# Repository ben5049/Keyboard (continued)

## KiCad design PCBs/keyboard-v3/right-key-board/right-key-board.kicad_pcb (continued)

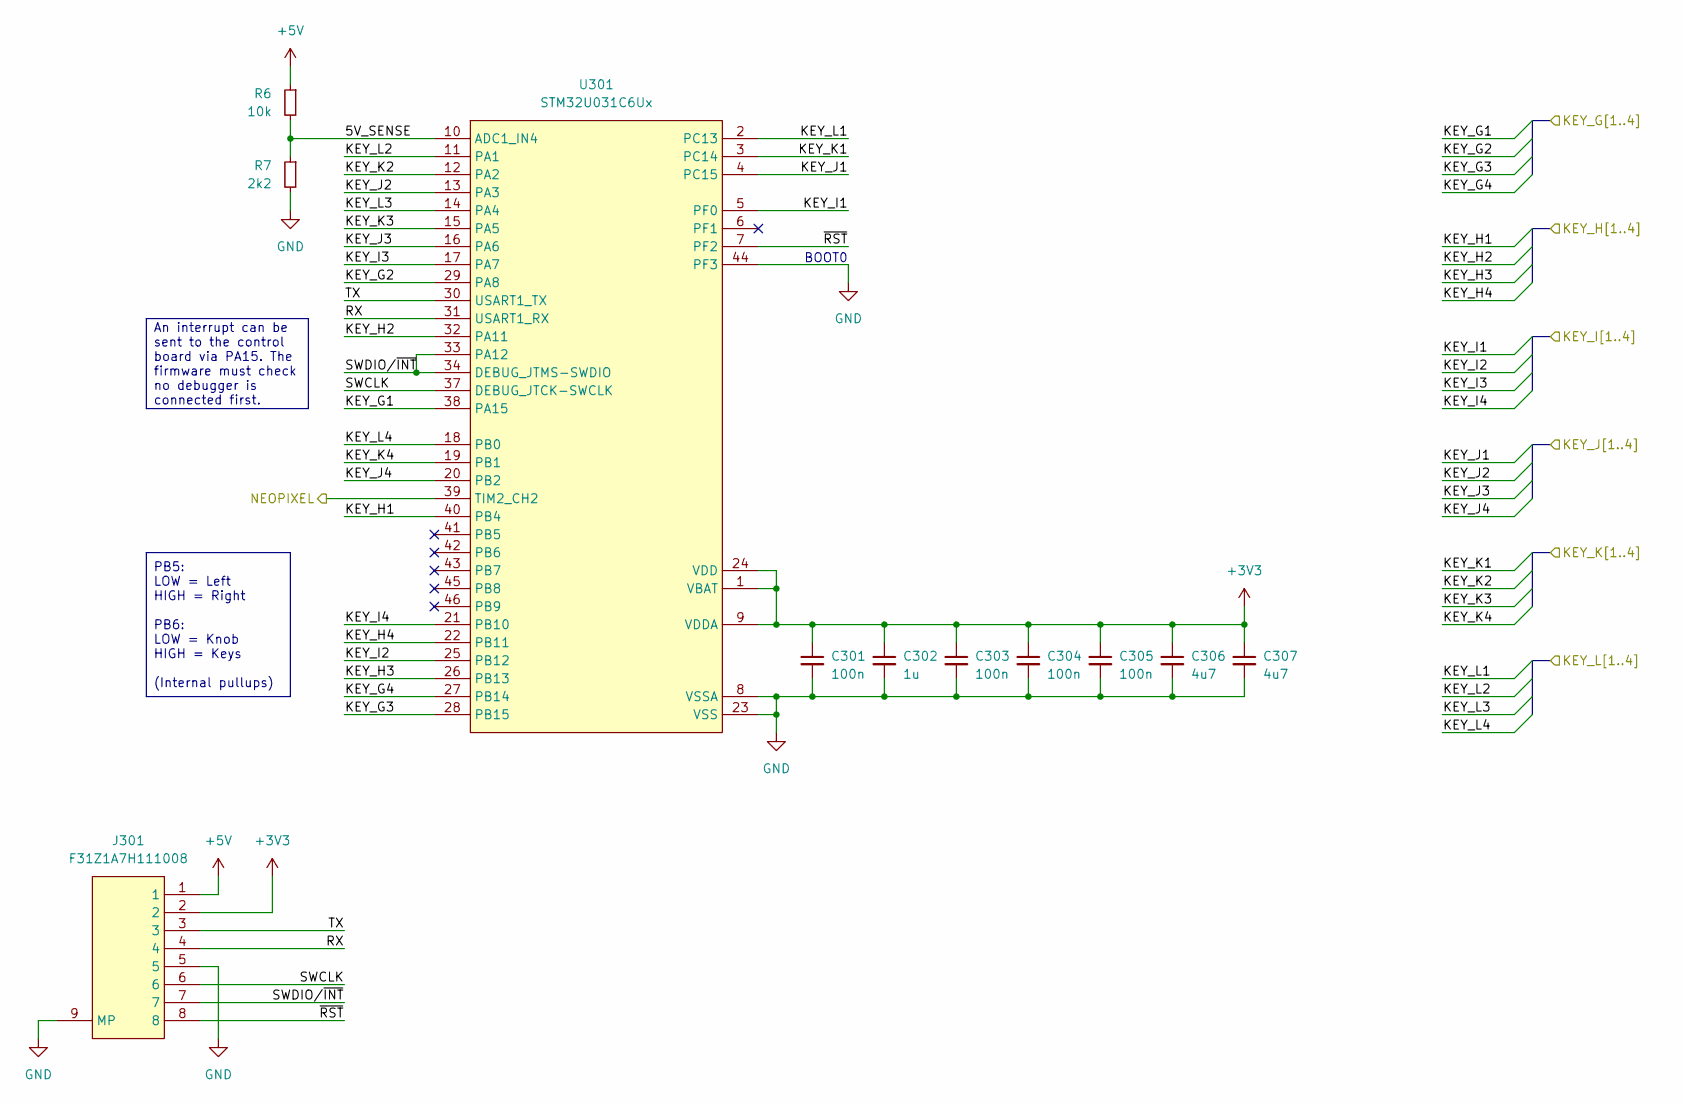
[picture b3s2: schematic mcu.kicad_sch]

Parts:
C301, C303, C304, C305: 100n; C_0402
C302: 1u; C_0402
C306, C307: 4u7; C_0402
J301: F31Z1A7H111008
R6: 10k; R_0402
R7: 2k2; R_0402
U301: STM32U031C6Ux; QFN50P700X700X60-49N-D

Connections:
+3V3: C301.1, C302.1, C303.1, C304.1, C305.1, C306.1, C307.1, J301.2, U301.1 (VBAT), U301.9 (VDDA), U301.24 (VDD), U301.36 (VDD), U301.48 (VDD)
+5V: J301.1, R6.1; also elsewhere on the board
/Keys/KEY_G1: U301.38 (PA15); also elsewhere on the board
/Keys/KEY_G2: U301.29 (PA8); also elsewhere on the board
/Keys/KEY_G3: U301.28 (PB15); also elsewhere on the board
/Keys/KEY_G4: U301.27 (PB14); also elsewhere on the board
/Keys/KEY_H1: U301.40 (PB4); also elsewhere on the board
/Keys/KEY_H2: U301.32 (PA11); also elsewhere on the board
/Keys/KEY_H3: U301.26 (PB13); also elsewhere on the board
/Keys/KEY_H4: U301.22 (PB11); also elsewhere on the board
/Keys/KEY_I1: U301.5 (PF0); also elsewhere on the board
/Keys/KEY_I2: U301.25 (PB12); also elsewhere on the board
/Keys/KEY_I3: U301.17 (PA7); also elsewhere on the board
/Keys/KEY_I4: U301.21 (PB10); also elsewhere on the board
/Keys/KEY_J1: U301.4 (PC15); also elsewhere on the board
/Keys/KEY_J2: U301.13 (PA3); also elsewhere on the board
/Keys/KEY_J3: U301.16 (PA6); also elsewhere on the board
/Keys/KEY_J4: U301.20 (PB2); also elsewhere on the board
/Keys/KEY_K1: U301.3 (PC14); also elsewhere on the board
/Keys/KEY_K2: U301.12 (PA2); also elsewhere on the board
/Keys/KEY_K3: U301.15 (PA5); also elsewhere on the board
/Keys/KEY_K4: U301.19 (PB1); also elsewhere on the board
/Keys/KEY_L1: U301.2 (PC13); also elsewhere on the board
/Keys/KEY_L2: U301.11 (PA1); also elsewhere on the board
/Keys/KEY_L3: U301.14 (PA4); also elsewhere on the board
/Keys/KEY_L4: U301.18 (PB0); also elsewhere on the board
/Keys/NEOPIXEL: U301.39 (TIM2_CH2); also elsewhere on the board
/MCU/5V_SENSE: R6.2, R7.1, U301.10 (ADC1_IN4)
/MCU/RX: J301.4, U301.31 (USART1_RX)
/MCU/SWCLK: J301.6, U301.37 (DEBUG_JTCK-SWCLK)
/MCU/SWDIO/~INT: J301.7, U301.33 (PA12), U301.34 (DEBUG_JTMS-SWDIO)
/MCU/TX: J301.3, U301.30 (USART1_TX)
/MCU/~RST: J301.8, U301.7 (PF2)
GND: C301.2, C302.2, C303.2, C304.2, C305.2, C306.2, C307.2, J301.5, J301.9 (MP), J301.10 (MP), J301.11 (MP), J301.12 (MP), R7.2, U301.8 (VSSA), U301.23 (VSS), U301.35 (VSS), U301.44 (PF3), U301.47 (VSS), U301.49 (VSS); also elsewhere on the board

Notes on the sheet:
BOOT0
An interrupt can be sent to the control board via PA15. The firmware must check no debugger is connected first.
PB5: LOW = Left HIGH = Right PB6: LOW = Knob HIGH = Keys (Internal pullups)

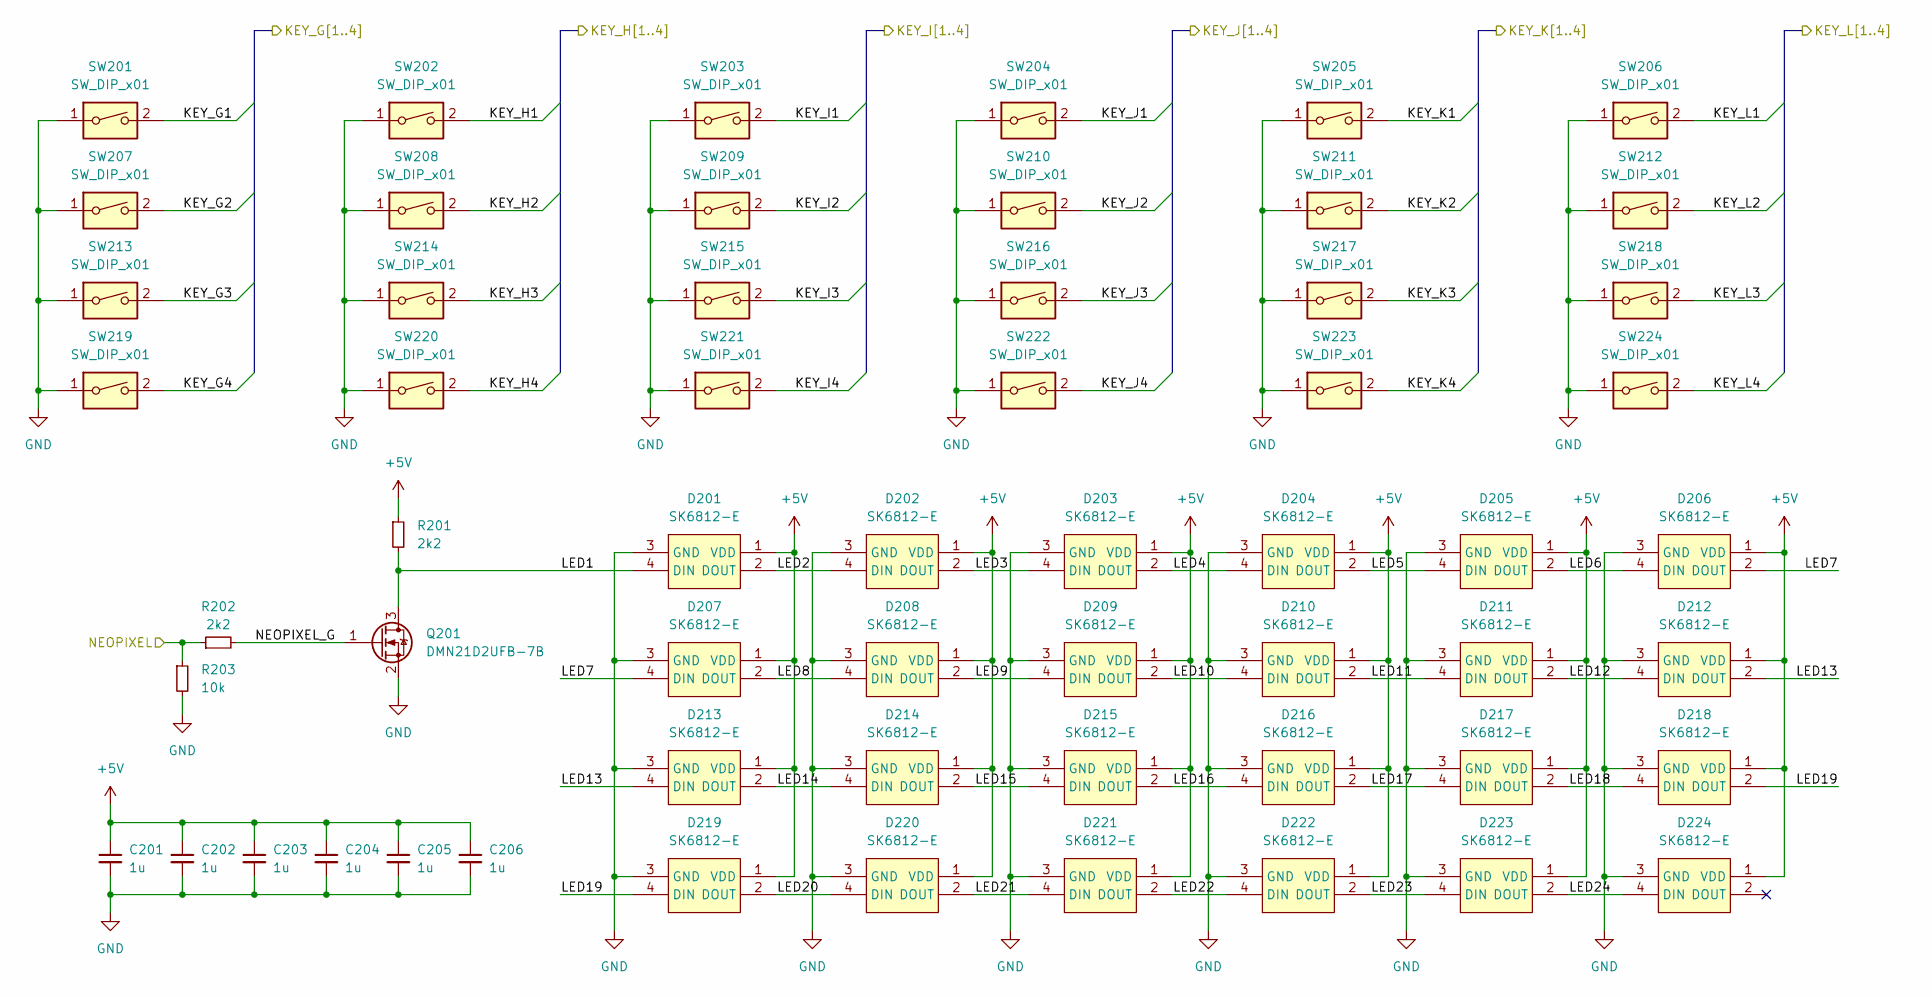
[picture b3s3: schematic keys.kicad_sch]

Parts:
C201, C202, C203, C204, C205, C206: 1u; C_0402
D201, D202, D203, D204, D205, D206, D207, D208, D209, D210, D211, D212, D213, D214, D215, D216, D217, D218, D219, D220, D221, D222, D223, D224: SK6812-E; sk6812-e; PARTREV 2
Q201: DMN21D2UFB-7B; DMN21D2UFB7B; Mouser Part Number 621-DMN21D2UFB-7B
R201, R202: 2k2; R_0402
R203: 10k; R_0402
SW201, SW202, SW203, SW204, SW205, SW206, SW207, SW208, SW209, SW210, SW211, SW212, SW213, SW214, SW215, SW216, SW217, SW218, SW219, SW220, SW221, SW222, SW223, SW224: SW_DIP_x01; SW_Kailh_Choc_V1_HotSwap

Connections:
+5V: C201.1, C202.1, C203.1, C204.1, C205.1, C206.1, D201.1 (VDD), D202.1 (VDD), D203.1 (VDD), D204.1 (VDD), D205.1 (VDD), D206.1 (VDD), D207.1 (VDD), D208.1 (VDD), D209.1 (VDD), D210.1 (VDD), D211.1 (VDD), D212.1 (VDD), D213.1 (VDD), D214.1 (VDD), D215.1 (VDD), D216.1 (VDD), D217.1 (VDD), D218.1 (VDD), D219.1 (VDD), D220.1 (VDD), D221.1 (VDD), D222.1 (VDD), D223.1 (VDD), D224.1 (VDD), R201.1; also elsewhere on the board
/Keys/KEY_G1: SW201.2; also elsewhere on the board
/Keys/KEY_G2: SW207.2; also elsewhere on the board
/Keys/KEY_G3: SW213.2; also elsewhere on the board
/Keys/KEY_G4: SW219.2; also elsewhere on the board
/Keys/KEY_H1: SW202.2; also elsewhere on the board
/Keys/KEY_H2: SW208.2; also elsewhere on the board
/Keys/KEY_H3: SW214.2; also elsewhere on the board
/Keys/KEY_H4: SW220.2; also elsewhere on the board
/Keys/KEY_I1: SW203.2; also elsewhere on the board
/Keys/KEY_I2: SW209.2; also elsewhere on the board
/Keys/KEY_I3: SW215.2; also elsewhere on the board
/Keys/KEY_I4: SW221.2; also elsewhere on the board
/Keys/KEY_J1: SW204.2; also elsewhere on the board
/Keys/KEY_J2: SW210.2; also elsewhere on the board
/Keys/KEY_J3: SW216.2; also elsewhere on the board
/Keys/KEY_J4: SW222.2; also elsewhere on the board
/Keys/KEY_K1: SW205.2; also elsewhere on the board
/Keys/KEY_K2: SW211.2; also elsewhere on the board
/Keys/KEY_K3: SW217.2; also elsewhere on the board
/Keys/KEY_K4: SW223.2; also elsewhere on the board
/Keys/KEY_L1: SW206.2; also elsewhere on the board
/Keys/KEY_L2: SW212.2; also elsewhere on the board
/Keys/KEY_L3: SW218.2; also elsewhere on the board
/Keys/KEY_L4: SW224.2; also elsewhere on the board
/Keys/LED1: D201.4 (DIN), Q201.3 (D), R201.2
/Keys/LED2: D201.2 (DOUT), D202.4 (DIN)
/Keys/LED3: D202.2 (DOUT), D203.4 (DIN)
/Keys/LED4: D203.2 (DOUT), D204.4 (DIN)
/Keys/LED5: D204.2 (DOUT), D205.4 (DIN)
/Keys/LED6: D205.2 (DOUT), D206.4 (DIN)
/Keys/LED7: D206.2 (DOUT), D207.4 (DIN)
/Keys/LED8: D207.2 (DOUT), D208.4 (DIN)
/Keys/LED9: D208.2 (DOUT), D209.4 (DIN)
/Keys/LED10: D209.2 (DOUT), D210.4 (DIN)
/Keys/LED11: D210.2 (DOUT), D211.4 (DIN)
/Keys/LED12: D211.2 (DOUT), D212.4 (DIN)
/Keys/LED13: D212.2 (DOUT), D213.4 (DIN)
/Keys/LED14: D213.2 (DOUT), D214.4 (DIN)
/Keys/LED15: D214.2 (DOUT), D215.4 (DIN)
/Keys/LED16: D215.2 (DOUT), D216.4 (DIN)
/Keys/LED17: D216.2 (DOUT), D217.4 (DIN)
/Keys/LED18: D217.2 (DOUT), D218.4 (DIN)
/Keys/LED19: D218.2 (DOUT), D219.4 (DIN)
/Keys/LED20: D219.2 (DOUT), D220.4 (DIN)
/Keys/LED21: D220.2 (DOUT), D221.4 (DIN)
/Keys/LED22: D221.2 (DOUT), D222.4 (DIN)
/Keys/LED23: D222.2 (DOUT), D223.4 (DIN)
/Keys/LED24: D223.2 (DOUT), D224.4 (DIN)
/Keys/NEOPIXEL: R202.1, R203.1; also elsewhere on the board
/Keys/NEOPIXEL_G: Q201.1 (G), R202.2
GND: C201.2, C202.2, C203.2, C204.2, C205.2, C206.2, D201.3 (GND), D202.3 (GND), D203.3 (GND), D204.3 (GND), D205.3 (GND), D206.3 (GND), D207.3 (GND), D208.3 (GND), D209.3 (GND), D210.3 (GND), D211.3 (GND), D212.3 (GND), D213.3 (GND), D214.3 (GND), D215.3 (GND), D216.3 (GND), D217.3 (GND), D218.3 (GND), D219.3 (GND), D220.3 (GND), D221.3 (GND), D222.3 (GND), D223.3 (GND), D224.3 (GND), Q201.2 (S), R203.2, SW201.1, SW202.1, SW203.1, SW204.1, SW205.1, SW206.1, SW207.1, SW208.1, SW209.1, SW210.1, SW211.1, SW212.1, SW213.1, SW214.1, SW215.1, SW216.1, SW217.1, SW218.1, SW219.1, SW220.1, SW221.1, SW222.1, SW223.1, SW224.1; also elsewhere on the board

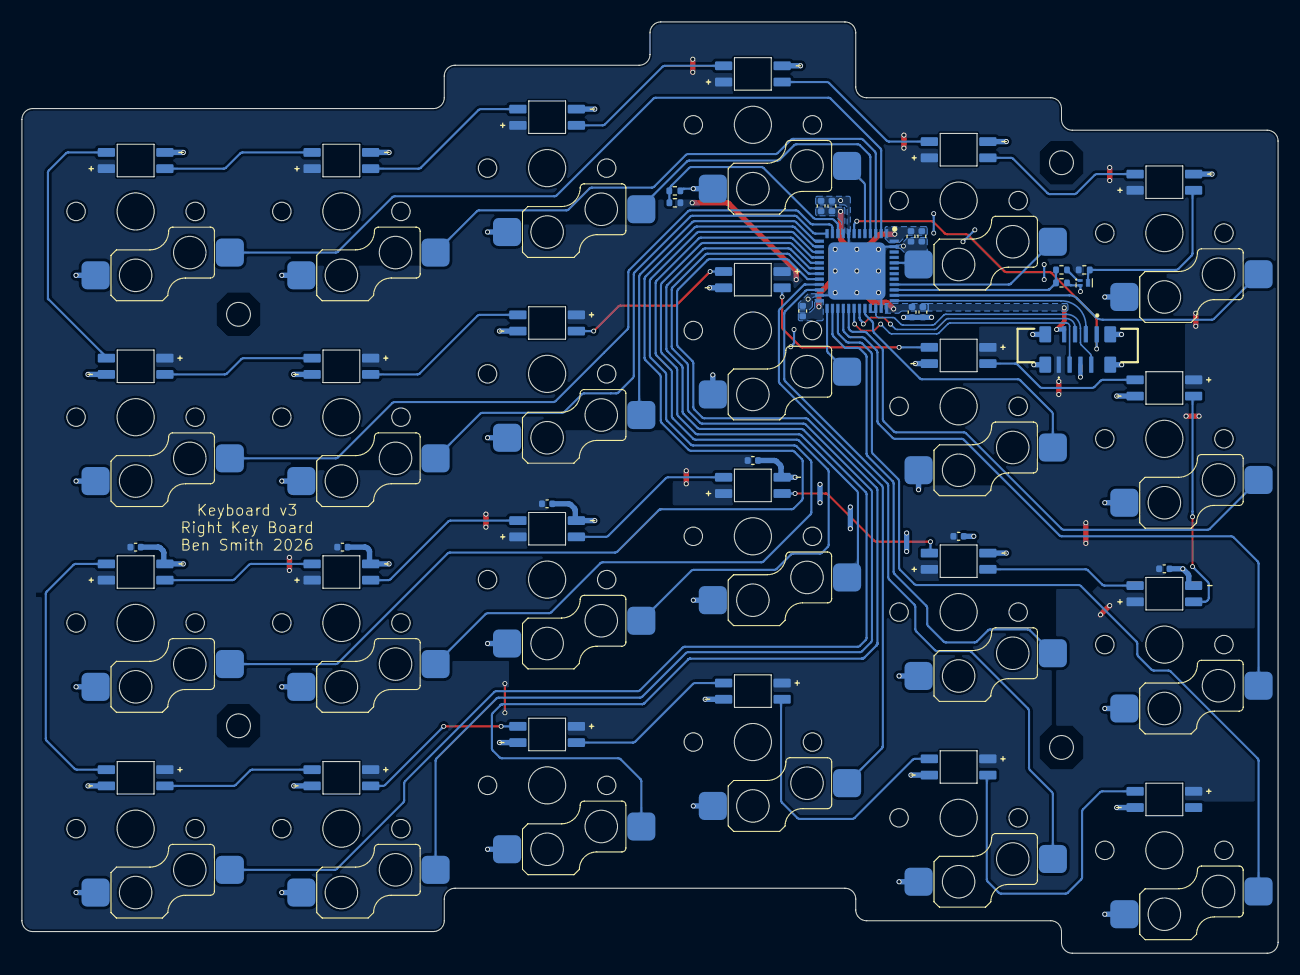
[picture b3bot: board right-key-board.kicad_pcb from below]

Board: 2 copper layers, 116.0 x 86.0 mm, 73 parts (49 on the bottom side), 59 nets.

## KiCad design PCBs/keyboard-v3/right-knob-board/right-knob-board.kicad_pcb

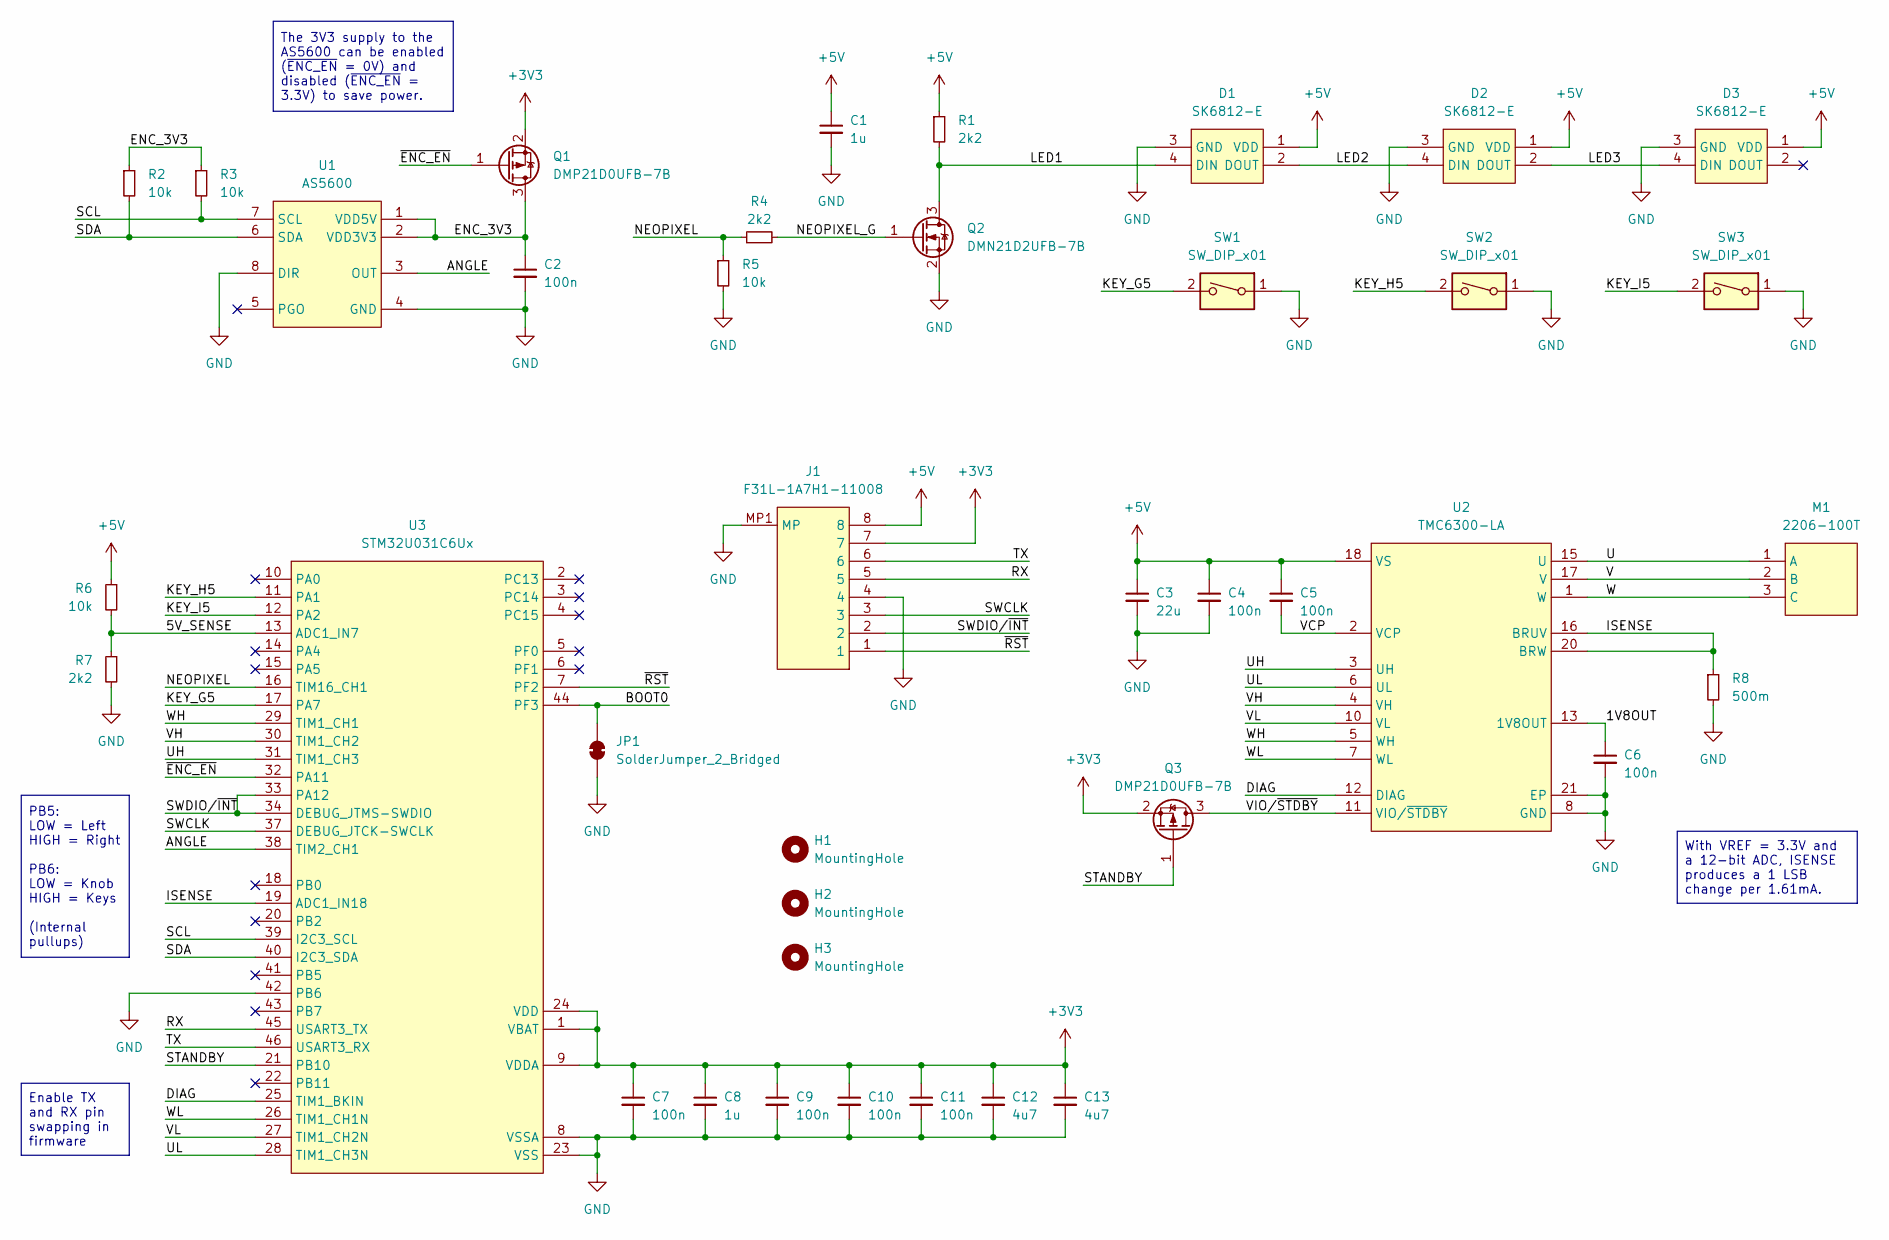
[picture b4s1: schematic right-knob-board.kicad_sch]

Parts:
C1, C8: 1u; C_0402
C2, C4, C5, C6, C7, C9, C10, C11: 100n; C_0402
C3: 22u; C_0603
C12, C13: 4u7; C_0402
D1, D2, D3: SK6812-E; sk6812-e; PARTREV 2
H1, H2, H3: MountingHole; MountingHole_2.2mm_M2
J1: F31L-1A7H1-11008
JP1: SolderJumper_2_Bridged; SolderJumper-2_P1.3mm_Bridged_RoundedPad1.0x1.5mm
M1: 2206-100T
Q1, Q3: DMP21D0UFB-7B; DMP21D0UFB7B; Mouser Part Number 621-DMP21D0UFB-7B
Q2: DMN21D2UFB-7B; DMN21D2UFB7B; Mouser Part Number 621-DMN21D2UFB-7B
R1, R4, R7: 2k2; R_0402
R2, R3, R5, R6: 10k; R_0402
R8: 500m; R_0402
SW1, SW2, SW3: SW_DIP_x01; SW_Kailh_Choc_V1_HotSwap
U1: AS5600; as5600-rear-magnet
U2: TMC6300-LA; QFN40P300X300X90-21N
U3: STM32U031C6Ux; QFN50P700X700X60-49N-D

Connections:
+3V3: C7.1, C8.1, C9.1, C10.1, C11.1, C12.1, C13.1, J1.7, Q1.2 (S), Q3.2 (S), U3.1 (VBAT), U3.9 (VDDA), U3.24 (VDD), U3.36 (VDD), U3.48 (VDD)
+5V: C1.1, C3.1, C4.1, C5.1, D1.1 (VDD), D2.1 (VDD), D3.1 (VDD), J1.8, R1.1, R6.1, U2.18 (VS)
/1V8OUT: C6.1, U2.13 (1V8OUT)
/5V_SENSE: R6.2, R7.1, U3.13 (ADC1_IN7)
/ANGLE: U1.3 (OUT), U3.38 (TIM2_CH1)
/BOOT0: JP1.2 (B), U3.44 (PF3)
/DIAG: U2.12 (DIAG), U3.25 (TIM1_BKIN)
/ENC_3V3: C2.1, Q1.3 (D), R2.1, R3.1, U1.1 (VDD5V), U1.2 (VDD3V3)
/ISENSE: R8.1, U2.16 (BRUV), U2.20 (BRW), U3.19 (ADC1_IN18)
/KEY_G5: SW1.2, U3.17 (PA7)
/KEY_H5: SW2.2, U3.11 (PA1)
/KEY_I5: SW3.2, U3.12 (PA2)
/LED1: D1.4 (DIN), Q2.3 (D), R1.2
/LED2: D1.2 (DOUT), D2.4 (DIN)
/LED3: D2.2 (DOUT), D3.4 (DIN)
/NEOPIXEL: R4.1, R5.1, U3.16 (TIM16_CH1)
/NEOPIXEL_G: Q2.1 (G), R4.2
/RX: J1.5, U3.45 (USART3_TX)
/SCL: R3.2, U1.7 (SCL), U3.39 (I2C3_SCL)
/SDA: R2.2, U1.6 (SDA), U3.40 (I2C3_SDA)
/STANDBY: Q3.1 (G), U3.21 (PB10)
/SWCLK: J1.3, U3.37 (DEBUG_JTCK-SWCLK)
/SWDIO/~INT: J1.2, U3.33 (PA12), U3.34 (DEBUG_JTMS-SWDIO)
/TX: J1.6, U3.46 (USART3_RX)
/U: M1.1 (A), U2.15 (U)
/UH: U2.3 (UH), U3.31 (TIM1_CH3)
/UL: U2.6 (UL), U3.28 (TIM1_CH3N)
/V: M1.2 (B), U2.17 (V)
/VCP: C5.2, U2.2 (VCP)
/VH: U2.4 (VH), U3.30 (TIM1_CH2)
/VIO/~STDBY: Q3.3 (D), U2.11 (VIO/~STDBY)
/VL: U2.10 (VL), U3.27 (TIM1_CH2N)
/W: M1.3 (C), U2.1 (W)
/WH: U2.5 (WH), U3.29 (TIM1_CH1)
/WL: U2.7 (WL), U3.26 (TIM1_CH1N)
/~ENC_EN: Q1.1 (G), U3.32 (PA11)
/~RST: J1.1, U3.7 (PF2)
GND: C1.2, C2.2, C3.2, C4.2, C6.2, C7.2, C8.2, C9.2, C10.2, C11.2, C12.2, C13.2, D1.3 (GND), D2.3 (GND), D3.3 (GND), J1.4, J1.MP1 (MP), J1.MP2 (MP), JP1.1 (A), Q2.2 (S), R5.2, R7.2, R8.2, SW1.1, SW2.1, SW3.1, U1.4 (GND), U1.8 (DIR), U2.8 (GND), U2.9 (GND), U2.14 (GND), U2.21 (EP), U3.8 (VSSA), U3.23 (VSS), U3.35 (VSS), U3.42 (PB6), U3.47 (VSS), U3.49 (VSS)

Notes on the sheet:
The 3V3 supply to the AS5600 can be enabled (~{ENC_EN} = 0V) and disabled (~{ENC_EN} = 3.3V) to save power.
Enable TX and RX pin swapping in firmware
With VREF = 3.3V and a 12-bit ADC, ISENSE produces a 1 LSB change per 1.61mA.
PB5: LOW = Left HIGH = Right PB6: LOW = Knob HIGH = Keys (Internal pullups)

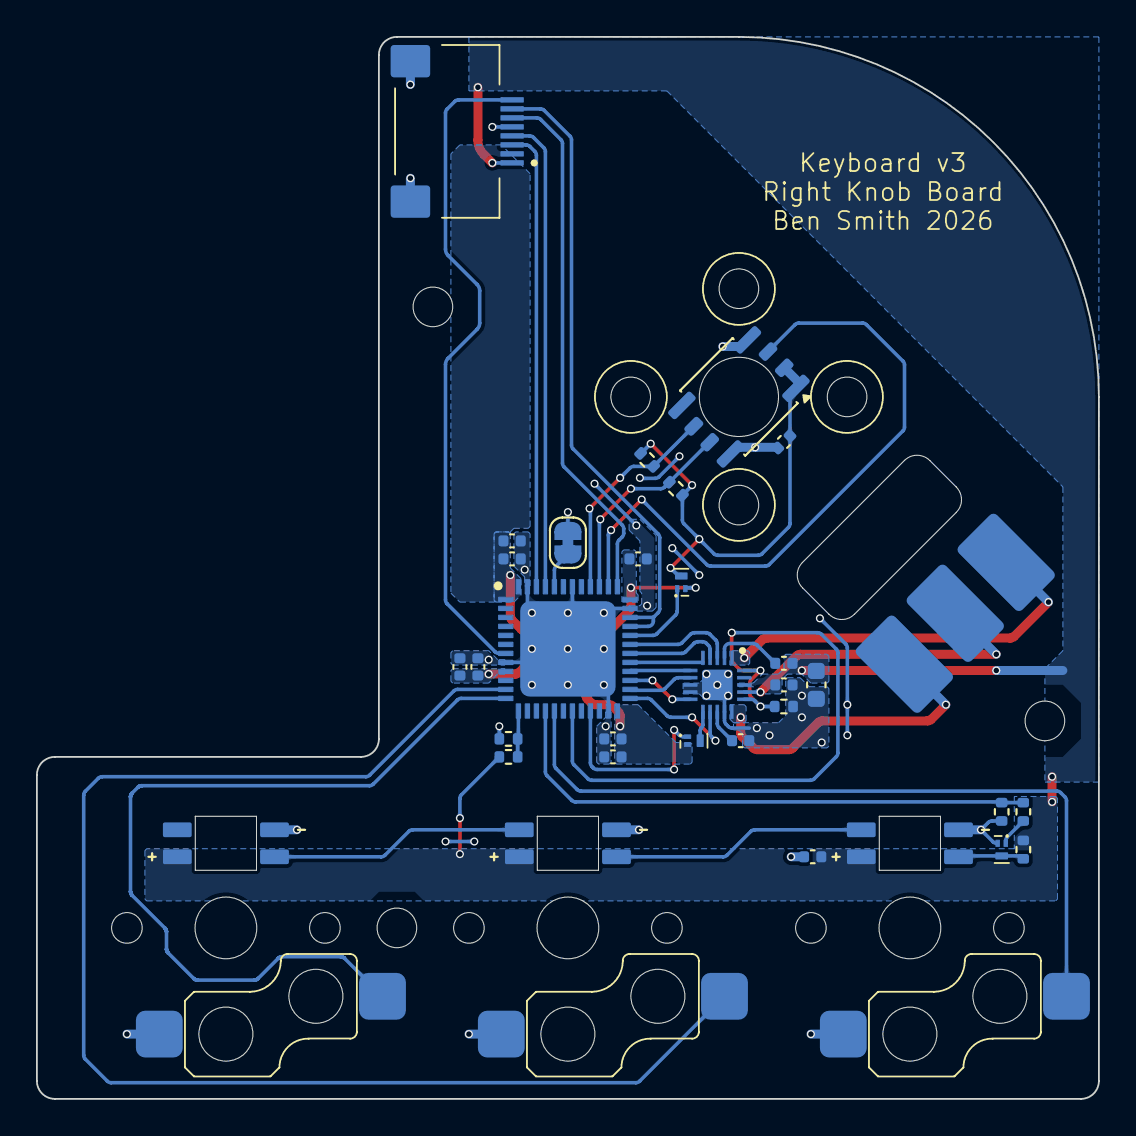
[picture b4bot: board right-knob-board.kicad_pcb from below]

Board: 2 copper layers, 59.0 x 59.0 mm, 39 parts (33 on the bottom side), 38 nets.
